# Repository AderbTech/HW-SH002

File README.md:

# HW-SH002
Smart Home Alarm Keypad

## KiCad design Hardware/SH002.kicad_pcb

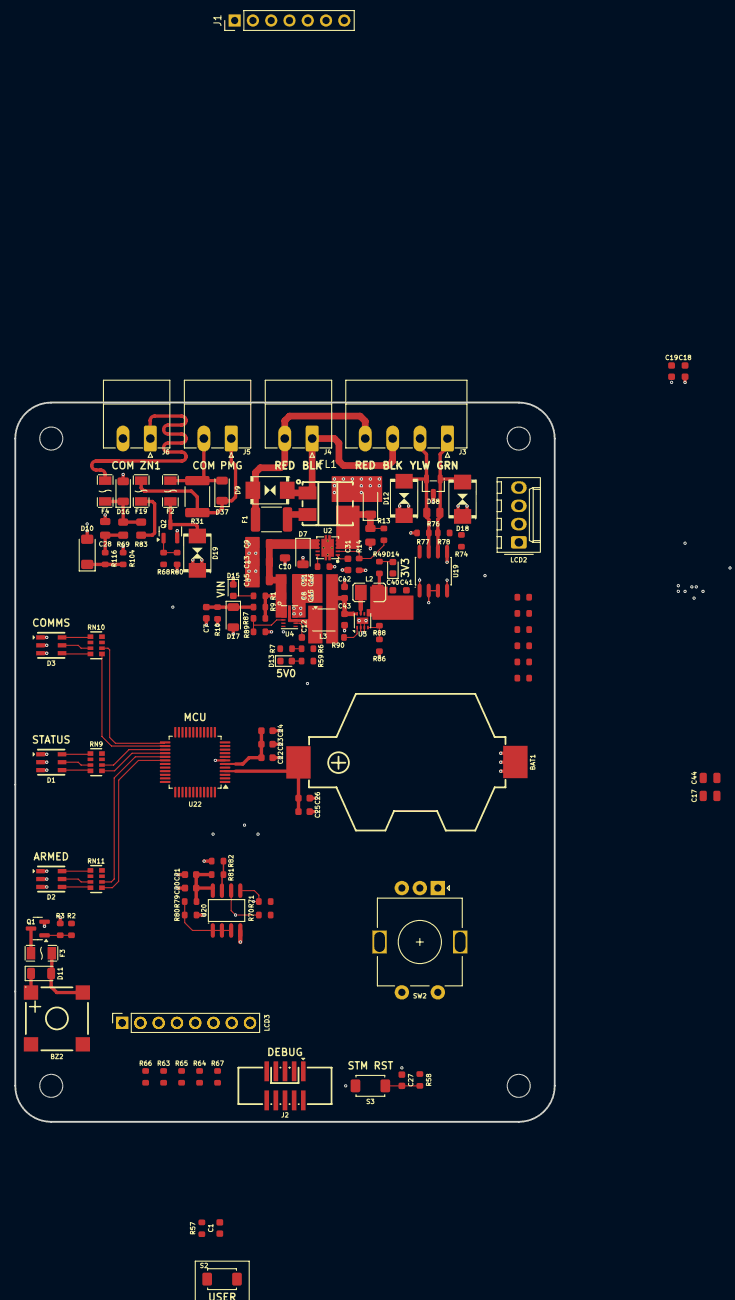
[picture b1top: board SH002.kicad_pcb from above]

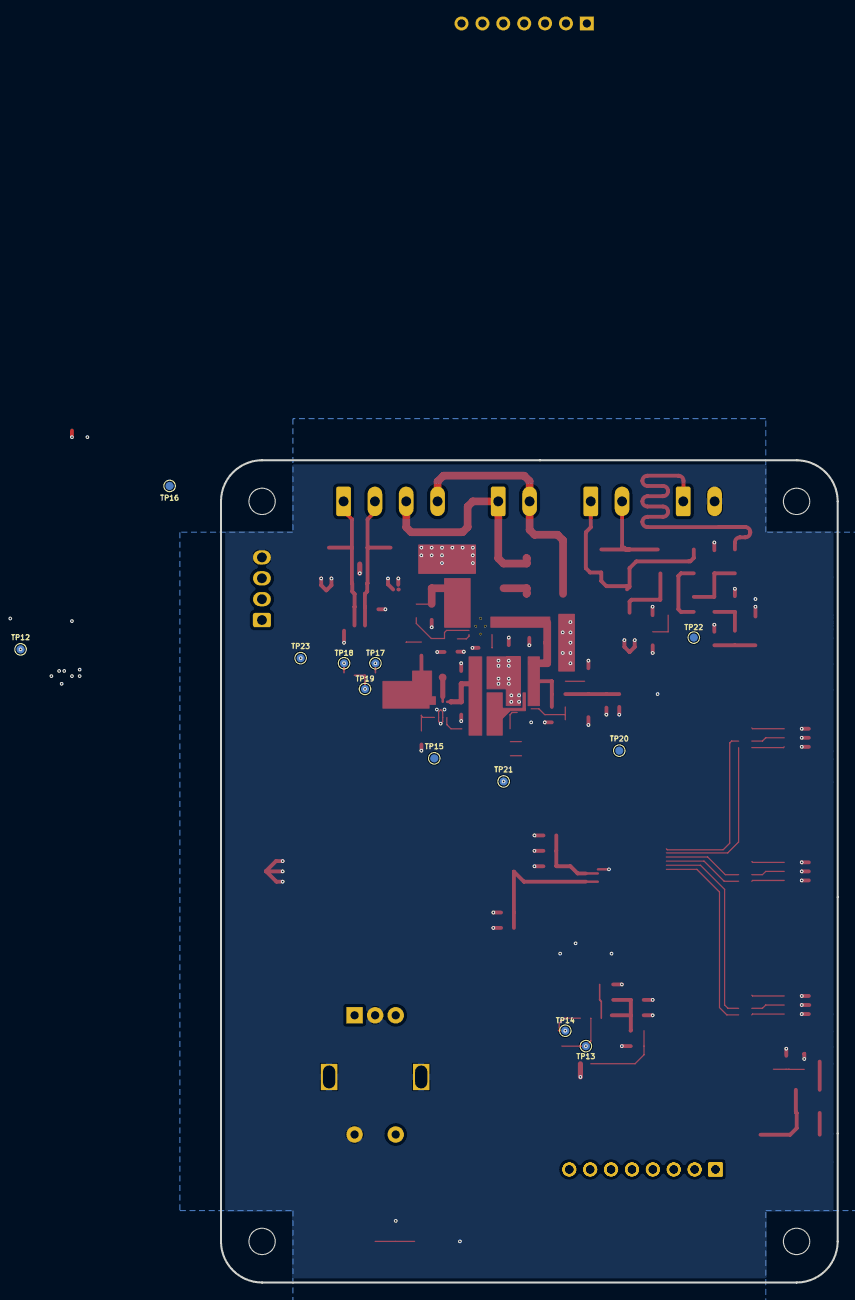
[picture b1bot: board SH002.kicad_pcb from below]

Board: 2 copper layers, 75.0 x 100.0 mm, 144 parts (12 on the bottom side), 84 nets.

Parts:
BAT1: 796136-1; BAT-SMD_796136-1
BZ2: SMD-8503-3627-16Ω; BUZ-SMD_4P-L8.5-W8.5-BR-1
C1, C7, C12, C19, C21, C24, C26, C27, C43: 100nF; C_0603
C6: 10uF; C_0805
C9, C10, C11, C13, C15, C16, C17, C44: 22uF; C_0805
C18, C20, C22, C42: 10uF; C_0603
C23, C25: 1uF; C_0603
C28, C30: 100nF; C_0805
C31: 4.7nF; C_0603
C40, C41: 22uF; C_0603
C45: CL21A475KBQNNNE; C_0805
D1, D2, D3: NH-Z3535RGBA-SG; LED-ARRAY-SMD_6P-L3.7-W3.5-TL-RD
D6, D7: SMF12A; D_SOD-123FL
D9, D12, D18, D19: P0640SCLRP; SMB_L4.6-W3.6-LS5.3-BI
D10: BZV55B3V6; D_MiniMELF
D11, D37: 1N4001W; D_SOD-123FL
D13, D14, D15: Red; D_0603
D16, D17: SMF5.0A; D_SOD-123FL
D38: SM712; SOT-23-3_L2.9-W1.3-P1.90-LS2.4-BR
F1: MF-MSMF110/16-2; Fuse_1812_4532Metric_Pad1.30x3.40mm_HandSolder
F2, F3, F4: JK-NSMD012; F1206
F19: ASMD1206-200-16V; F1206
FL1: ACM70V-701-2PL-TL00; FILTER-SMD_4P-L7.0-W6.0-TL_ACM70V
H1, H2, H3, H4: MountingHole; MountingHole_3.2mm_M3_ISO14580
J1: Conn_01x07; Keypad_3X4
J2: Connector, USB-TYPE-C-16P; IDC-SMD_10P-P1.27-3220-10-0300-00
J3: Conn_01x04; PhoenixContact_MC_1,5_4-G-3.81_1x04_P3.81mm_Horizontal
J4, J5, J6: Conn_01x02; PhoenixContact_MC_1,5_2-G-3.81_1x02_P3.81mm_Horizontal
L2: 4.7uH 2.2A; L1008
L3: L; L_Coilcraft_1008HQ_2520Metric
LCD2: 20X4 I2C; Molex_KK-254_AE-6410-04A_1x04_P2.54mm_Vertical
LCD3: ST7735 2.79in SPI; LCD 2.79 INCH SPI HEADER NMH
LCD4: ST7735 2.79in SPI; LCD 2.79 INCH SPI ST7789
Q1, Q2: 2N7002K; Q_SOT-23
R1: 1kΩ; R_0603
R2, R63, R64, R68, R72, R73, R91: 49.9Ω; R_0603
R3, R57, R58, R60, R65, R66, R67, R74, R75, R79, R80, R81, R82, R84, R85, R116: 10kΩ; R_0603
R6, R9: 100kΩ; R_0603
R7, R10, R86: 33kΩ; R_0603
R11: 47kΩ; R_0603
R13, R87, R90: 1MΩ; R_0603
R14: 330kΩ; R_0603
R31: HMLV1812-470G; R_1812_4532Metric_Pad1.30x3.40mm_HandSolder
R49, R59, R77, R78: 330Ω; R_0603
R69: 1kΩ; R_0805
R70, R71: 4.7kΩ; R_0603
R76: 120Ω; R_0805
R83: 10kΩ; R_0805
R88, R89: 220kΩ; R_0603
R104: 3.3kΩ; R_0603
RN9, RN10, RN11: 4D03WGJ0471T5E; RES-ARRAY-SMD_0603-8P-L3.2-W1.6-BL
S2, S3: Tactile Button, 160gf; SW_TS-1088-AR02016
SW2: RotaryEncoder_Switch_MP; RotaryEncoder_Alps_EC11E-Switch_Vertical_H20mm
TP12: 3V3; TestPoint_Pad_D1.0mm
TP13: SCL; TestPoint_Pad_D1.0mm
TP14: SDA; TestPoint_Pad_D1.0mm
TP15: 5V0; TestPoint_Pad_D1.0mm
TP16: GND; TestPoint_Pad_D1.0mm
TP17: 485_RX; TestPoint_Pad_D1.0mm
TP18: 485_TX; TestPoint_Pad_D1.0mm
TP19: 485_DE; TestPoint_Pad_D1.0mm
TP20: VSYS; TestPoint_Pad_D1.0mm
TP21: VFB; TestPoint_Pad_D1.0mm
TP22: TestPoint; TestPoint_Pad_D1.0mm
TP23: 5V0_EN; TestPoint_Pad_D1.0mm
U2: TPS259251DRCR; WSON-10_L3.0-W3.0-P0.50-BL-EP
U3: TLV62080DSGR; WSON-8-1EP_2x2mm_P0.5mm_EP0.9x1.6mm
U4: AP63357DV-7; V-DFN3020-13-A_L3.0-W2.0-P0.45-BL-EP_AP6335X
U19: SP3485EN; SOIC-8_L5.0-W4.0-P1.27-LS6.0-BL
U20: AT24C256C; SOIC-8_L4.9-W3.9-P1.27-LS6.0-BL
U22: MCU, STM32G0B0CETx; LQFP-48_7x7mm_P0.5mm

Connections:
+3V3: BZ2.1, C18.1, C19.1, C20.1, C21.1, C22.1, C23.1, C24.1, C40.1, C41.1, D11.1, J2.8 (VDD), L2.2, LCD2.3, LCD3.7 (VDD), R49.1, R57.1, R58.1, R65.1, R66.1, R67.1, R70.1, R71.1, R75.1, R78.1, R79.1, R81.1, R84.1, R85.1, R88.1, TP12.1 (1_1), U3.5 (VOS), U19.8 (VCC), U20.8 (VCC), U22.6 (VDD)
+5V0: C15.1, C16.1, C17.1, C42.1, C43.1, C44.1, L3.2, R6.1, R59.1, R90.1, TP15.1 (1_1), U3.8 (VIN)
+VADC: F19.2, R83.1
+VBAT: BAT1.1 (+), C25.1, C26.1, U22.4 (VBAT)
+VSYS: C6.1, C9.1, C10.1, C11.1, C13.1, C45.1, D7.1, D37.1, F19.1, J5.1, R1.1, R9.1, R31.1, R87.1, TP20.1 (1_1), U2.6 (OUT), U2.7 (OUT), U2.8 (OUT), U4.1 (VIN)
/ADC_ZONE/ADC_MCU: D10.1 (K), R104.1, R116.1
/ADC_ZONE/ADC_RAW: F4.2, J6.1
/AW21024/AW_SCL: R70.2, TP13.1 (1_1), U20.6 (SCL), U22.33 (PA11)
/AW21024/AW_SDA: R71.2, TP14.1 (1_1), U20.5 (SDA), U22.34 (PA12)
/BUZZER/BUZZ: R2.1, U22.38 (PD0)
/DEBUG/RST/EN: C27.1, J2.3 (RST/EN), R58.2, S3.2 (B), U22.10 (NRST)
/DEBUG/RXD: J2.9 (RXD), U22.40 (PD2)
/DEBUG/SWCLK: J2.2 (SWCLK), U22.36 (PA14)
/DEBUG/SWDIO: J2.1 (SWDIO), U22.35 (PA13)
/DEBUG/TXD: J2.10 (TXD), U22.41 (PD3)
/EXPANSION/485_DE_~RE: R74.1, TP19.1 (1_1), U19.2 (RE#), U19.3 (DE), U22.39 (PD1)
/EXPANSION/485_N: D12.2, D38.2, J3.2, R76.1, R77.1, U19.7 (B)
/EXPANSION/485_P: D18.2, D38.1, J3.1, R76.2, R78.2, U19.6 (A)
/EXPANSION/485_RX: TP17.1 (1_1), U19.1 (RO), U22.45 (PB6)
/EXPANSION/485_TX: TP18.1 (1_1), U19.4 (DI), U22.46 (PB7)
/KEYPAD/KET_C3: J1.7, U22.19 (PB0)
/KEYPAD/KEY_C1: J1.5, U22.14 (PA3)
/KEYPAD/KEY_C2: J1.6, U22.17 (PA6)
/KEYPAD/KEY_R1: J1.1, U22.20 (PB1)
/KEYPAD/KEY_R2: J1.2, U22.21 (PB2)
/KEYPAD/KEY_R3: J1.3, U22.22 (PB10)
/KEYPAD/KEY_R4: J1.4, U22.18 (PA7)
/LED_STATUS/LED_ACT: RN9.5 (R4.2), U22.28 (PA8)
/LED_STATUS/LED_ARMED: RN11.6 (R3.2), U22.29 (PA9)
/LED_STATUS/LED_CONFIG: RN10.6 (R3.2), U22.25 (PB13)
/LED_STATUS/LED_LINK: RN9.6 (R3.2), U22.27 (PB15)
/LED_STATUS/LED_RUN: RN10.5 (R4.2), U22.26 (PB14)
/LED_STATUS/LED_TRIP: RN11.5 (R4.2), U22.30 (PC6)
/LED_STATUS/USER_BTN: C1.1, R57.2, S2.2 (B), U22.31 (PC7)
/MEMORY/EE_WP: R81.2, R82.1, U20.7 (WP)
/PGM/EXT_LED: R68.1, U22.37 (PA15)
/PGM/EXT_LED_RTN: D37.2, F2.1, J5.2, R31.2
/POWER/PWR_5V0/SW: C12.2, L3.1, U4.7 (NC), U4.9 (SW)
/POWER/VSYS_ADC: C7.1, D17.1, R9.2, R10.1, U22.12 (PA1)
/ST7735/LCD_BL: LCD3.1 (BL), U22.23 (PB11)
/ST7735/LCD_CS: LCD3.2 (CS), R66.2, U22.43 (PB4)
/ST7735/LCD_DC: LCD3.3 (DC), U22.32 (PA10)
/ST7735/LCD_MOSI: R64.1, U22.44 (PB5)
/ST7735/LCD_RST: LCD3.4 (RES), U22.24 (PB12)
/ST7735/LCD_SCK: R63.2, U22.42 (PB3)
GND: BAT1.2 (-), C1.2, C6.2, C7.2, C9.2, C10.2, C11.2, C13.2, C15.2, C16.2, C17.2, C18.2, C19.2, C20.2, C21.2, C22.2, C23.2, C24.2, C25.2, C26.2, C27.2, C28.2, C30.2, C31.2, C40.2, C41.2, C42.2, C43.2, C44.2, C45.2, D1.1 (RK), D1.2 (GK), D1.3 (BK), D2.1 (RK), D2.2 (GK), D2.3 (BK), D3.1 (RK), D3.2 (GK), D3.3 (BK), D6.2, D7.2, D10.2 (A), D12.1, D13.1, D14.1, D15.1, D16.2, D17.2, D18.1, D19.1, D38.3, FL1.4, J2.7 (VSS), J6.2, LCD2.4, LCD3.8 (GND), Q1.2 (S), Q2.2 (S), R3.2, R7.2, R10.2, R11.2, R14.2, R60.2, R74.2, R77.2, R80.2, R82.2, R86.2, R89.2, R104.2, S2.1 (A), S3.1 (A), SW2.C, SW2.MP, SW2.S2, TP16.1 (1_1), U2.11 (GND), U3.2 (GND), U3.3 (GND), U3.9 (GND), U4.4 (COMP), U4.8 (GND), U19.5 (GND), U20.4 (GND), U22.7 (VSS)
unnamed: BZ2.2, D11.2, F3.1
unnamed: C28.1, R69.1, R116.2, TP22.1 (1_1)
unnamed: D1.4 (BA), RN9.4 (R4.1)
unnamed: D1.5 (GA), RN9.3 (R3.1)
unnamed: D1.6 (RA), RN9.1 (R1.1)
unnamed: D2.4 (BA), RN11.4 (R4.1)
unnamed: D2.5 (GA), RN11.3 (R3.1)
unnamed: D2.6 (RA), RN11.1 (R1.1)
unnamed: D3.4 (BA), RN10.4 (R4.1)
unnamed: D3.5 (GA), RN10.3 (R3.1)
unnamed: D3.6 (RA), RN10.1 (R1.1)
unnamed: D13.2, R59.2
unnamed: D14.2, R49.2
unnamed: D15.2, R1.2
unnamed: D16.1, F4.1, R69.2, R83.2
unnamed: F1.1, FL1.2
unnamed: LCD3.6 (SCL), R64.2, R67.2
unnamed: LCD3.5 (SDA), R63.1, R65.2
unnamed: F3.2, Q1.3 (D)
unnamed: Q1.1 (G), R2.2, R3.1
unnamed: D19.2, F2.2, Q2.3 (D)
unnamed: Q2.1 (G), R60.1, R68.2
unnamed: R72.2, R85.2, SW2.A
unnamed: R73.1, R84.2, SW2.B
unnamed: R75.2, R91.1, SW2.S1
unnamed: R13.2, R14.1, U2.2 (EN/UVLO)
unnamed: R11.1, U2.10 (ILIM)
unnamed: C31.1, U2.1 (dV/dT)
unnamed: R90.2, U3.1 (EN)
unnamed: R86.1, R88.2, U3.4 (FB)
unnamed: L2.1, U3.7 (SW)
unnamed: C12.1, U4.6 (BST)
unnamed: R87.2, R89.1, TP23.1 (1_1), U4.2 (EN)
unnamed: R6.2, R7.1, TP21.1 (1_1), U4.3 (FB)
unnamed: R79.2, R80.1, U20.1 (A0), U20.2 (A1), U20.3 (A2)
PWR+: D9.2, F1.2, J3.4, J4.2
PWR-: D9.1, FL1.1, J3.3, J4.1
VPROT: C30.1, D6.1, FL1.3, R13.1, U2.3 (VIN), U2.4 (VIN), U2.5 (VIN)

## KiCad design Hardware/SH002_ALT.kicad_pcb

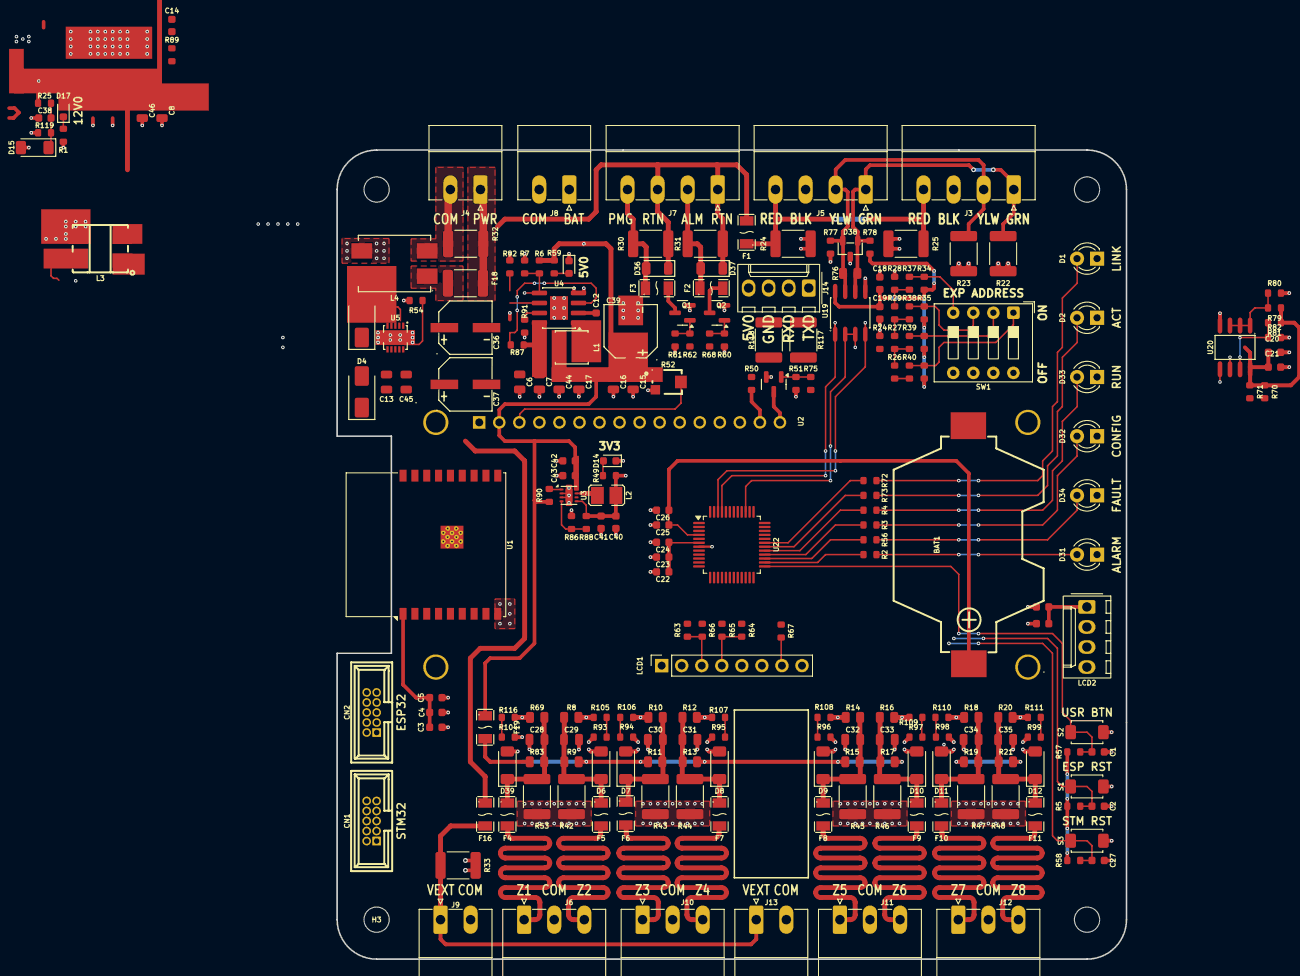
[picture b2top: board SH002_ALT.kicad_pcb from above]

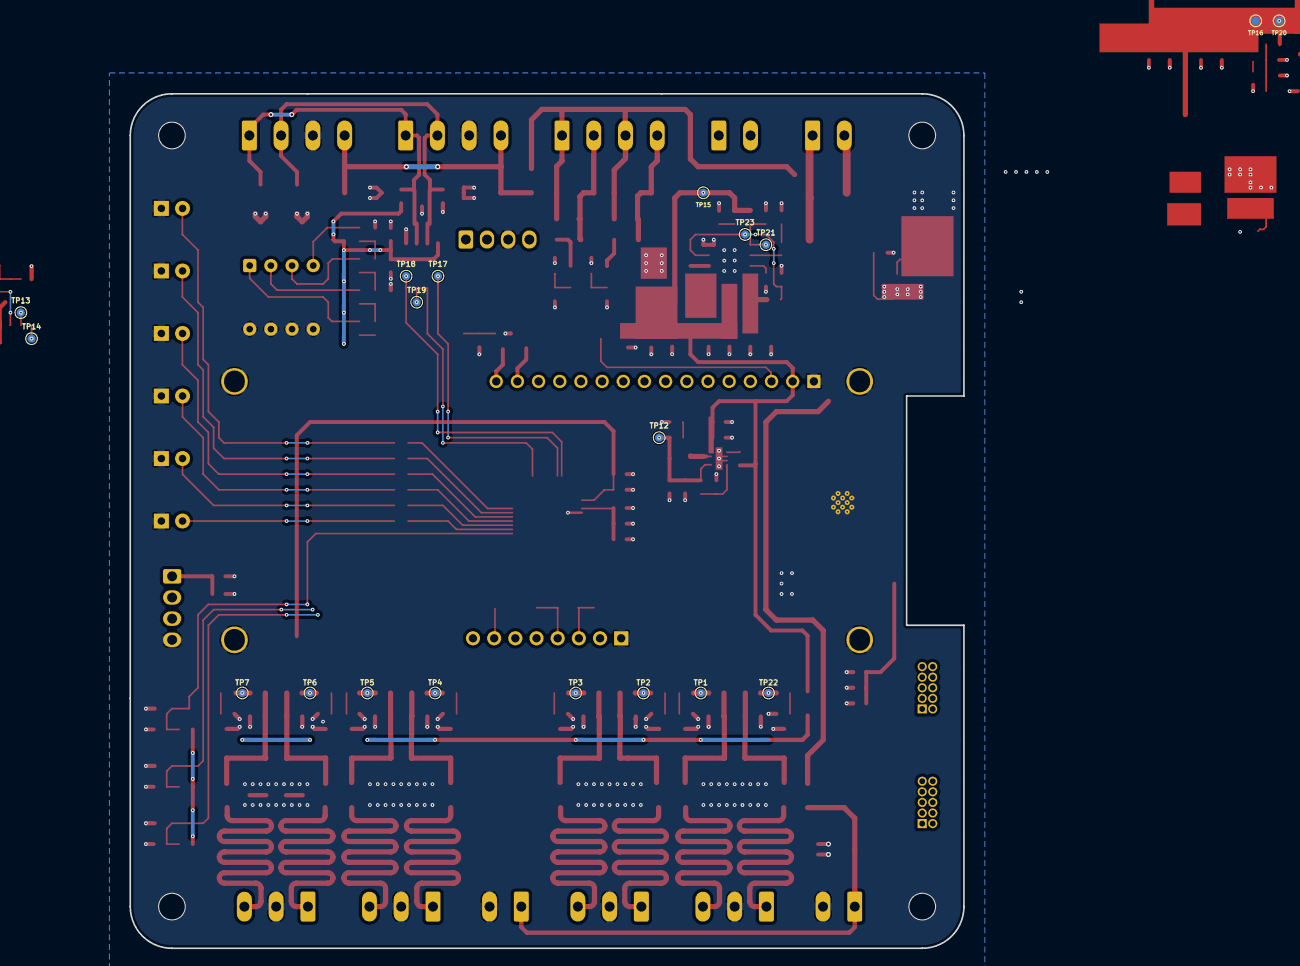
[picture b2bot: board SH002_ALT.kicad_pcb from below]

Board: 2 copper layers, 100.0 x 102.5 mm, 250 parts (19 on the bottom side), 124 nets.

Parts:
BAT1: 796136-1; BAT-SMD_796136-1
C1, C2, C5, C10, C12, C19, C21, C24, C26, C27, C38, C43: 100nF; C_0603
C3, C18, C20, C22, C42: 10uF; C_0603
C4, C9, C23, C25: 1uF; C_0603
C6, C7: 10uF; C_0805
C8, C45: CL21A475KBQNNNE; C_0805
C13, C15, C16, C17, C44, C46: 22uF; C_0805
C14: 2.7nF; C_0603
C28, C29, C30, C31, C32, C33, C34, C35: 100nF; C_0805
C36, C37, C39: 16V 100uF; CAP-SMD_BD6.3-L6.6-W6.6-LS7.2-FD
C40, C41: 22uF; C_0603
CN1, CN2: HX JN1.27-2X5 TP H4.9; IDC-TH_10P-P1.27-V-M-R2-C5-S1.27
D1, D2, D31, D32, D33, D34: LED; LED_D3.0mm
D4, D16: SMAJ28CA; D_SMA
D6, D7, D8, D9, D10, D11, D12, D15, D39: BZV55B3V6; D_MiniMELF
D13, D14, D17: Red; D_0603
D36, D37: 1N4001W; D_SOD-123FL
D38: SM712; SOT-23-3_L2.9-W1.3-P1.90-LS2.4-BR
F1, F16, F19: ASMD1206-200-16V; F1206
F2, F3, F4, F5, F6, F7, F8, F9, F10, F11: JK-NSMD012; F1206
F18: Fuse; R_1812_4532Metric_Pad1.30x3.40mm_HandSolder
H1, H2, H3, H4: MountingHole; MountingHole_3.2mm_M3_ISO14580
J3, J5, J7: Conn_01x04; PhoenixContact_MC_1,5_4-G-3.81_1x04_P3.81mm_Horizontal
J4, J8, J9, J13: Conn_01x02; PhoenixContact_MC_1,5_2-G-3.81_1x02_P3.81mm_Horizontal
J6, J10, J11, J12: Conn_01x03; PhoenixContact_MC_1,5_3-G-3.81_1x03_P3.81mm_Horizontal
J14: Conn_01x04; Molex_KK-254_AE-6410-04A_1x04_P2.54mm_Vertical
L1: IND, 6.8uH 2.8A; IND-SMD_L4.0-W4.0
L2: 4.7uH 2.2A; L1008
L3: ACM70V-701-2PL-TL00; FILTER-SMD_4P-L7.0-W6.0-TL_ACM70V
L4: SMCM9070-701T; FILTER-SMD_4P-L9.0-W7.0-LS9.5-1
LCD1: ST7735 1.8in SPI; LCD, ST7735 1.8in SPI
LCD2: Conn_01x04; Molex_KK-254_AE-6410-04A_1x04_P2.54mm_Vertical
Q1, Q2, Q4: 2N7002K; Q_SOT-23
R1: 1kΩ; R_0603
R2, R3, R4, R49, R50, R56, R59, R72, R73, R77, R78: 330Ω; R_0603
R5, R34, R35, R36, R37, R38, R39, R40, R41, R51, R57, R58, R60, R61, R65, R66, R67, R74, R79, R80, R81, R82, R105, R106, R107, R108, R109, R110, R111, R116: 10kΩ; R_0603
R6, R25, R54: 100kΩ; R_0603
R7, R86, R119: 33kΩ; R_0603
R8, R10, R12, R14, R16, R18, R20, R69: 1kΩ; R_0805
R9, R11, R13, R15, R17, R19, R21, R83: 10kΩ; R_0805
R22, R23, R24, R25#2, R30, R31, R32, R33, R42, R43, R44, R45, R46, R47, R48, R53, R117, R118: HMLV1812-470G; R_1812_4532Metric_Pad1.30x3.40mm_HandSolder
R26, R27, R28, R29: 5.1kΩ; R_0603
R52: TC33X-2-103E; RES-ADJ-SMD_3P-L3.0-W3.8-P1.75-BR
R62, R63, R64, R68, R75: 49.9Ω; R_0603
R70, R71: 4.7kΩ; R_0603
R76: 120Ω; R_0805
R87, R90: 1MΩ; R_0603
R88, R89: 220kΩ; R_0603
R91: 56kΩ; R_0603
R92: 12kΩ; R_0603
R93, R94, R95, R96, R97, R98, R99, R104: 3.3kΩ; R_0603
S1, S2, S3: Tactile Button, 160gf; SW_TS-1088-AR02016
SW1: SW_DIP_x04; SW_DIP_SPSTx04_Slide_9.78x12.34mm_W7.62mm_P2.54mm
TP1, TP2, TP3, TP4, TP5, TP6, TP7, TP22: TestPoint; TestPoint_Pad_D1.0mm
TP12: 3V3; TestPoint_Pad_D1.0mm
TP13: SCL; TestPoint_Pad_D1.0mm
TP14: SDA; TestPoint_Pad_D1.0mm
TP15: 5V0; TestPoint_Pad_D1.0mm
TP16: GND; TestPoint_Pad_D1.0mm
TP17: 485_RX; TestPoint_Pad_D1.0mm
TP18: 485_TX; TestPoint_Pad_D1.0mm
TP19: 485_DE; TestPoint_Pad_D1.0mm
TP20: VSYS; TestPoint_Pad_D1.0mm
TP21: VFB; TestPoint_Pad_D1.0mm
TP23: 5V0_EN; TestPoint_Pad_D1.0mm
U1: ESP32-C3-WROOM-02
U2: HS1602A-B; LCD1602
U3: TLV62080DSGR; WSON-8-1EP_2x2mm_P0.5mm_EP0.9x1.6mm
U4: RT7272BGSP; SOIC-8-1EP_3.9x4.9mm_P1.27mm_EP2.29x3mm
U5: TPS259260DRCR; VSON-10_L3.0-W3.0-P0.50-TL-EP-1
U19: SP3485EN; SOIC-8_L5.0-W4.0-P1.27-LS6.0-BL
U20: AT24C256C; SOIC-8_L4.9-W3.9-P1.27-LS6.0-BL
U22: MCU, STM32G0B0CETx; LQFP-48_7x7mm_P0.5mm

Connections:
+3V3: C3.1, C4.1, C5.1, C9.1, C10.1, C18.1, C19.1, C20.1, C21.1, C22.1, C23.1, C24.1, C40.1, C41.1, CN1.8 (VDD), CN2.8 (VDD), L2.2, LCD1.2, LCD2.1, R5.1, R34.1, R35.1, R36.1, R41.1, R49.1, R57.1, R58.1, R65.1, R66.1, R67.1, R70.1, R71.1, R78.1, R79.1, R81.1, R88.1, TP12.1 (1_1), U1.1 (3V3), U3.5 (VOS), U19.8 (VCC), U20.8 (VCC), U22.6 (VDD)
+5V0: C15.1, C16.1, C17.1, C39.1, C42.1, C43.1, C44.1, F19.1, L1.2, R6.1, R50.2, R52.1, R59.1, R90.1, TP15.1 (1_1), U2.2 (VDD), U3.8 (VIN)
+VADC: F19.2, R9.1, R11.1, R13.1, R15.1, R17.1, R19.1, R21.1, R83.1
+VBAT: BAT1.1, C25.1, C26.1, U22.4 (VBAT)
+VSYS: C6.1, C7.1, C8.1, C13.1, C36.1, C37.1, C45.1, C46.1, D4.2, D17.2, D36.1, D37.1, F1.2, F16.1, J7.1, J7.3, R25.1, R30.1, R31.1, R87.1, TP20.1 (1_1), U4.8 (VIN), U5.6 (OUT), U5.7 (OUT), U5.8 (OUT)
/DEBUG1/RXD: CN2.9 (RXD), U1.12 (IO21/TXD)
/DEBUG1/SWO/GPIO: CN2.4 (SWO/GPIO), U1.8 (IO9)
/DEBUG1/TXD: CN2.10 (TXD), U1.11 (IO20/RXD)
/DEBUG1/USB_N: CN2.5 (USB_N), U1.14 (IO19)
/DEBUG1/USB_P: CN2.6 (USB_P), U1.13 (IO18)
/DEBUG/RST/EN: C27.1, CN1.3 (RST/EN), R58.2, S3.2 (B), U22.10 (NRST)
/DEBUG/RXD: CN1.9 (RXD), U22.40 (PD2)
/DEBUG/SWCLK: CN1.2 (SWCLK), U22.36 (PA14)
/DEBUG/SWDIO: CN1.1 (SWDIO), U22.35 (PA13)
/DEBUG/TXD: CN1.10 (TXD), U22.41 (PD3)
/ESP32C3/ESP_IO6: U1.5 (IO6), U22.48 (PB9)
/ESP32C3/ESP_IO7: U1.6 (IO7), U22.47 (PB8)
/ESP_EN: C2.1, CN2.3 (RST/EN), R5.2, S1.2 (B), U1.2 (EN), U22.1 (PC13)
/EXP_ADDR/485_ADC_ADDR: R26.2, R40.1, U22.11 (PA0)
/LCD BASIC/BL: LCD1.8, R75.2, U22.23 (PB11)
/LCD BASIC/D4: J14.1, R117.1, U2.11 (DB4), U22.16 (PA5)
/LCD BASIC/D5: J14.2, R118.1, U2.12 (DB5), U22.15 (PA4)
/LCD BASIC/D6: R64.1, U2.13 (DB6), U22.44 (PB5)
/LCD BASIC/D7: R63.2, U2.14 (DB7), U22.42 (PB3)
/LCD BASIC/E: LCD1.7, R67.2, U2.6 (E), U22.43 (PB4)
/LCD BASIC/RS: LCD1.5, U2.4 (RS), U22.24 (PB12)
/LCD BASIC/RW: LCD1.6, U2.5 (RW), U22.32 (PA10)
/MEMORY/EE_WP: R81.2, R82.1, U20.7 (WP)
/OUTPUTS/EXT_LED: R68.1, U22.37 (PA15)
/OUTPUTS/EXT_LED_RTN: D37.2, F2.1, J7.2, R31.2
/OUTPUTS/SIREN: R62.1, U22.38 (PD0)
/OUTPUTS/SIREN_RTN: D36.2, F3.1, J7.4, R30.2
/POWER/SW: C12.2, L1.1, U4.1 (SW)
/POWER/VSYS_ADC: C38.1, D15.1 (K), R25.2, R119.1, U22.12 (PA1)
/RS485/485_DE_~RE: R74.1, TP19.1 (1_1), U19.2 (RE#), U19.3 (DE), U22.39 (PD1)
/RS485/485_N: D38.2, J3.2, J5.2, R23.1, R76.1, R77.1, U19.7 (B)
/RS485/485_P: D38.1, J3.1, J5.1, R22.1, R76.2, R78.2, U19.6 (A)
/RS485/485_RX: TP17.1 (1_1), U19.1 (RO), U22.45 (PB6)
/RS485/485_TX: TP18.1 (1_1), U19.4 (DI), U22.46 (PB7)
/SCL: LCD2.3, R70.2, TP13.1 (1_1), U20.6 (SCL), U22.33 (PA11)
/SDA: LCD2.2, R71.2, TP14.1 (1_1), U20.5 (SDA), U22.34 (PA12)
/STATUS_LED/LED_ACT: R73.2, U22.30 (PC6)
/STATUS_LED/LED_CONFIG: R56.2, U22.27 (PB15)
/STATUS_LED/LED_FAULT: R3.2, U22.28 (PA8)
/STATUS_LED/LED_LINK: R72.2, U22.31 (PC7)
/STATUS_LED/LED_RUN: R4.2, U22.29 (PA9)
/STATUS_LED/LED_TRIP: R2.2, U22.26 (PB14)
/STATUS_LED/USER_BTN: C1.1, R57.2, S2.2 (B), U22.25 (PB13)
/STM32/PA02: R104.1, R116.1, U22.13 (PA2)
/STM32/PA03: R93.1, R105.1, U22.14 (PA3)
/STM32/PA06: R94.1, R106.1, U22.17 (PA6)
/STM32/PA07: R95.1, R107.1, U22.18 (PA7)
/STM32/PB00: R96.1, R108.1, U22.19 (PB0)
/STM32/PB01: R97.1, R109.1, U22.20 (PB1)
/STM32/PB02: R98.1, R110.1, U22.21 (PB2)
/STM32/PB10: R99.1, R111.1, U22.22 (PB10)
/VCOM: F1.1, J3.4, J5.4, R24.1, R25#2.1
/ZONES_8W/ADC_ZONE1/ADC_RAW: F5.2, J6.3
/ZONES_8W/ADC_ZONE2/ADC_RAW: F6.2, J10.1
/ZONES_8W/ADC_ZONE3/ADC_RAW: F7.2, J10.3
/ZONES_8W/ADC_ZONE4/ADC_RAW: F8.2, J11.1
/ZONES_8W/ADC_ZONE5/ADC_RAW: F9.2, J11.3
/ZONES_8W/ADC_ZONE6/ADC_RAW: F10.2, J12.1
/ZONES_8W/ADC_ZONE7/ADC_RAW: F11.2, J12.3
/ZONES_8W/ADC_ZONE/ADC_RAW: F4.2, J6.1
/ZONES_8W/VSYS_EXT1: F16.2, J9.1, J13.1, R33.1
GND: BAT1.2, C1.2, C2.2, C3.2, C4.2, C5.2, C6.2, C7.2, C8.2, C9.2, C10.2, C13.2, C15.2, C16.2, C17.2, C18.2, C19.2, C20.2, C21.2, C22.2, C23.2, C24.2, C25.2, C26.2, C27.2, C28.2, C29.2, C30.2, C31.2, C32.2, C33.2, C34.2, C35.2, C36.2, C37.2, C38.2, C39.2, C40.2, C41.2, C42.2, C43.2, C44.2, C45.2, C46.2, CN1.7 (VSS), CN2.7 (VSS), D1.1 (K), D2.1 (K), D4.1, D6.2 (A), D7.2 (A), D8.2 (A), D9.2 (A), D10.2 (A), D11.2 (A), D12.2 (A), D13.1, D14.1, D15.2 (A), D16.1, D31.1 (K), D32.1 (K), D33.1 (K), D34.1 (K), D38.3, D39.2 (A), J3.3, J5.3, J6.2, J9.2, J10.2, J11.2, J12.2, J13.2, J14.3, L4.3, LCD1.1, LCD2.4, Q1.2 (S), Q2.2 (S), Q4.2 (S), R1.2, R7.2, R22.2, R23.2, R24.2, R25#2.2, R28.2, R33.2, R42.2, R43.2, R44.2, R45.2, R46.2, R47.2, R48.2, R51.2, R52.3, R53.2, R54.2, R60.2, R61.2, R74.2, R77.2, R80.2, R82.2, R86.2, R89.2, R91.2, R92.2, R93.2, R94.2, R95.2, R96.2, R97.2, R98.2, R99.2, R104.2, R117.2, R118.2, R119.2, S1.1 (A), S2.1 (A), S3.1 (A), SW1.5, SW1.6, SW1.7, SW1.8, TP16.1 (1_1), U1.9 (GND), U1.19 (GND), U2.0 (EH), U2.1 (VSS), U3.2 (GND), U3.3 (GND), U3.9 (GND), U4.4 (GND), U4.9 (GND), U5.11 (GND), U19.5 (GND), U20.4 (GND), U22.7 (VSS)
unnamed: C14.2, R92.1
unnamed: D1.2 (A), R72.1
unnamed: D2.2 (A), R73.1
unnamed: C29.1, D6.1 (K), F5.1, R8.2, R9.2, R42.1
unnamed: C30.1, D7.1 (K), F6.1, R10.2, R11.2, R43.1
unnamed: C31.1, D8.1 (K), F7.1, R12.2, R13.2, R44.1
unnamed: C32.1, D9.1 (K), F8.1, R14.2, R15.2, R45.1
unnamed: C33.1, D10.1 (K), F9.1, R16.2, R17.2, R46.1
unnamed: C34.1, D11.1 (K), F10.1, R18.2, R19.2, R47.1
unnamed: C35.1, D12.1 (K), F11.1, R20.2, R21.2, R48.1
unnamed: D13.2, R59.2
unnamed: D14.2, R49.2
unnamed: D17.1, R1.1
unnamed: D31.2 (A), R2.1
unnamed: D32.2 (A), R3.1
unnamed: D33.2 (A), R4.1
unnamed: D34.2 (A), R56.1
unnamed: C28.1, D39.1 (K), F4.1, R53.1, R69.2, R83.2
unnamed: F18.2, L4.1
unnamed: LCD1.3, R63.1, R66.2
unnamed: LCD1.4, R64.2, R65.2
unnamed: F3.2, Q1.3 (D)
unnamed: Q1.1 (G), R61.1, R62.2
unnamed: F2.2, Q2.3 (D)
unnamed: Q2.1 (G), R60.1, R68.2
unnamed: Q4.3 (D), U2.16 (LED-)
unnamed: Q4.1 (G), R51.1, R75.1
unnamed: R10.1, R106.2, TP2.1 (1_1)
unnamed: R26.1, R27.2, R39.1
unnamed: R27.1, R29.2, R38.1
unnamed: R28.1, R29.1, R37.1
unnamed: R34.2, R37.2, SW1.4
unnamed: R35.2, R38.2, SW1.3
unnamed: R36.2, R39.2, SW1.2
unnamed: R40.2, R41.2, SW1.1
unnamed: R8.1, R105.2, TP1.1 (1_1)
unnamed: R12.1, R107.2, TP3.1 (1_1)
unnamed: R14.1, R108.2, TP4.1 (1_1)
unnamed: R16.1, R109.2, TP5.1 (1_1)
unnamed: R18.1, R110.2, TP6.1 (1_1)
unnamed: R20.1, R111.2, TP7.1 (1_1)
unnamed: R69.1, R116.2, TP22.1 (1_1)
unnamed: R50.1, U2.15 (LED+)
unnamed: R52.2, U2.3 (V0)
unnamed: R90.2, U3.1 (EN)
unnamed: R86.1, R88.2, U3.4 (FB)
unnamed: L2.1, U3.7 (SW)
unnamed: C12.1, U4.2 (BOOT)
unnamed: C14.1, U4.6 (COMP)
unnamed: R87.2, R89.1, TP23.1 (1_1), U4.3 (EN)
unnamed: R6.2, R7.1, TP21.1 (1_1), U4.5 (FB)
unnamed: R91.1, U4.7 (RLIM)
unnamed: D16.2, L4.4, U5.2 (EN/UVLO), U5.3 (VIN), U5.4 (VIN), U5.5 (VIN)
unnamed: R54.1, U5.10 (ILIM)
unnamed: R79.2, R80.1, U20.1 (A0), U20.2 (A1), U20.3 (A2)
PWR+: F18.1, J4.1, R32.1
PWR-: J4.2, L4.2, R32.2

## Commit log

2026-06-09 add initiail design files
    add initial design files and documents
2026-06-09 remove unused sheets
